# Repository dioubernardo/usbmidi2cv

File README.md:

# USB MIDI to CV

Project inspired by [elkayem/midi2cv](https://github.com/elkayem/midi2cv), but using MIDI over USB communication.

## Requirements

- Arduino Leonardo or any board based on ATmega32u4 or ARM ([MIDIUSB compatibility](https://docs.arduino.cc/libraries/midiusb/#Compatibility))  
- MCP4728 (PCBs are designed for the generic GY-MCP4728 module)  
- LM324N  
- Some resistors and connectors

> ⚠️ The resistors connected to the A output of the LM324N don't need to match exact values, as long as they maintain an amplification ratio of approximately 1.77. Inaccurate values may affect 1V/Oct tuning.

The operational amplifier is configured as a non-inverting amplifier with the following resistors:

- **R1 = 10kΩ** (between the inverting input and GND)
- **R2 = 6.8kΩ + 900Ω _(from trimpot)_ = 7.7kΩ** (between the output and the inverting input)

The amplification factor (gain) is calculated as:

Amplification = 1 + (R2/R1) = 1 + (7.7kΩ/10kΩ) = 1.77

Therefore, the gain is **1.77x**.

## How It Works

- When a MIDI note is received (regardless of channel), it is converted to CV in 1V/Oct format, with C0 = 0V, C1 = 1V, C2 = 2V... covering 88 notes total.
- When a second note is played, it replaces the previous one, which is kept in a buffer.
- **Velocity** is converted to a voltage ranging from 0V to 4V.
- A **Trigger Pulse** of 5V is sent for 20ms every time a note is triggered.
- The **Gate** stays high (5V) while any note is being played.
- **Pitch Bend** is centered at 0.5V and ranges from 0V to 1V.
- Any **Control Change (CC)** message is converted to a voltage from 0V to 4V.

## Schematic

The file [`usbmidi2cv.sch`](https://github.com/dioubernardo/usbmidi2cv/blob/main/usbmidi2cv.sch) contains the schematic and can be edited using Eagle.

## PCB

Designed to work as an Arduino shield, this PCB can be easily etched on a single-sided copper board for DIY builds.

The file [`usbmidi2cv.brd`](https://github.com/dioubernardo/usbmidi2cv/blob/main/usbmidi2cv.brd) contains the PCB layout, also editable in Eagle.

To print, use the file [pcb.pdf](https://github.com/dioubernardo/usbmidi2cv/blob/main/pcb.pdf).

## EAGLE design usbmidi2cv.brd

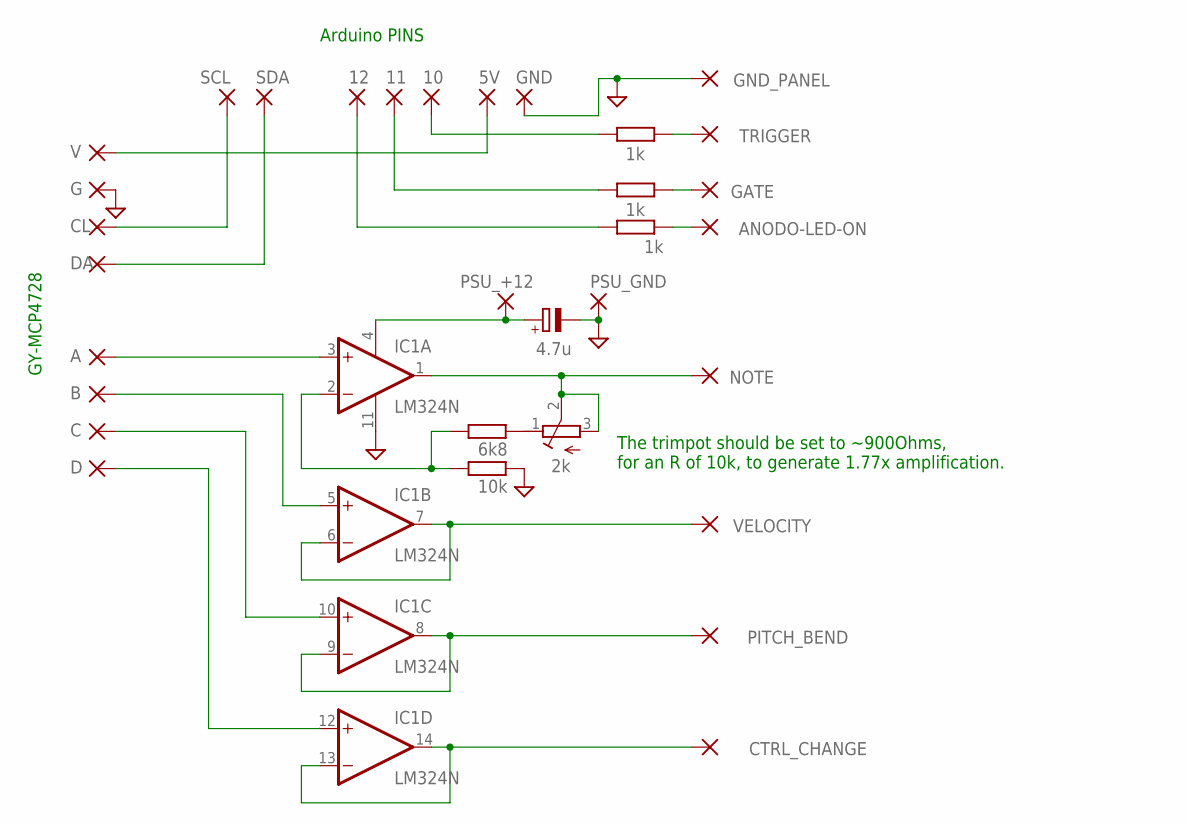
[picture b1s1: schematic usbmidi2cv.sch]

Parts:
5V, 10, 11, 12: 1,6/0,8
A: 1,6/0,8
ANODO-LED-ON: 1,6/0,8
B: 1,6/0,8
C: 1,6/0,8
C1: 4.7u; E2,5-6
CL: 1,6/0,8
CTRL_CHANGE: 1,6/0,8
D: 1,6/0,8
DA: 1,6/0,8
G: 1,6/0,8
GATE: 1,6/0,8
GND: 1,6/0,8
GND_PANEL: 1,6/0,8
IC1: LM324N; DIL14
NOTE: 1,6/0,8
PITCH_BEND: 1,6/0,8
PSU_+12: 1,6/0,8
PSU_GND: 1,6/0,8
R1, R2, R3: 1k; 0204/7
R4: 10k; 0207/12
R5: 2k; RTRIM3006P
R6: 6k8; 0207/12
SCL: 1,6/0,8
SDA: 1,6/0,8
TRIGGER: 1,6/0,8
V: 1,6/0,8
VELOCITY: 1,6/0,8

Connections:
GND: C1.-, G.1, GND.1, GND_PANEL.1, IC1.11 (V-), PSU_GND.1, R4.2
unnamed: A.1, IC1.3 (+IN)
unnamed: R2.1, TRIGGER.1
unnamed: GATE.1, R1.1
unnamed: 10.1, R2.2
unnamed: 11.1, R1.2
unnamed: ANODO-LED-ON.1, R3.1
unnamed: 12.1, R3.2
unnamed: 5V.1, V.1
unnamed: CL.1, SCL.1
unnamed: DA.1, SDA.1
unnamed: B.1, IC1.5 (+IN)
unnamed: C.1, IC1.10 (+IN)
unnamed: CTRL_CHANGE.1, IC1.13 (-IN), IC1.14 (OUT)
unnamed: IC1.1 (OUT), NOTE.1, R5.2 (S), R5.3 (A)
unnamed: IC1.8 (OUT), IC1.9 (-IN), PITCH_BEND.1
unnamed: IC1.6 (-IN), IC1.7 (OUT), VELOCITY.1
unnamed: IC1.2 (-IN), R4.1, R6.1
unnamed: R5.1 (E), R6.2
unnamed: C1.+, IC1.4 (V+), PSU_+12.1
unnamed: D.1, IC1.12 (+IN)

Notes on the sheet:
Arduino PINS
GY-MCP4728
The trimpot should be set to ~900Ohms, for an R of 10k, to generate 1.77x amplification.

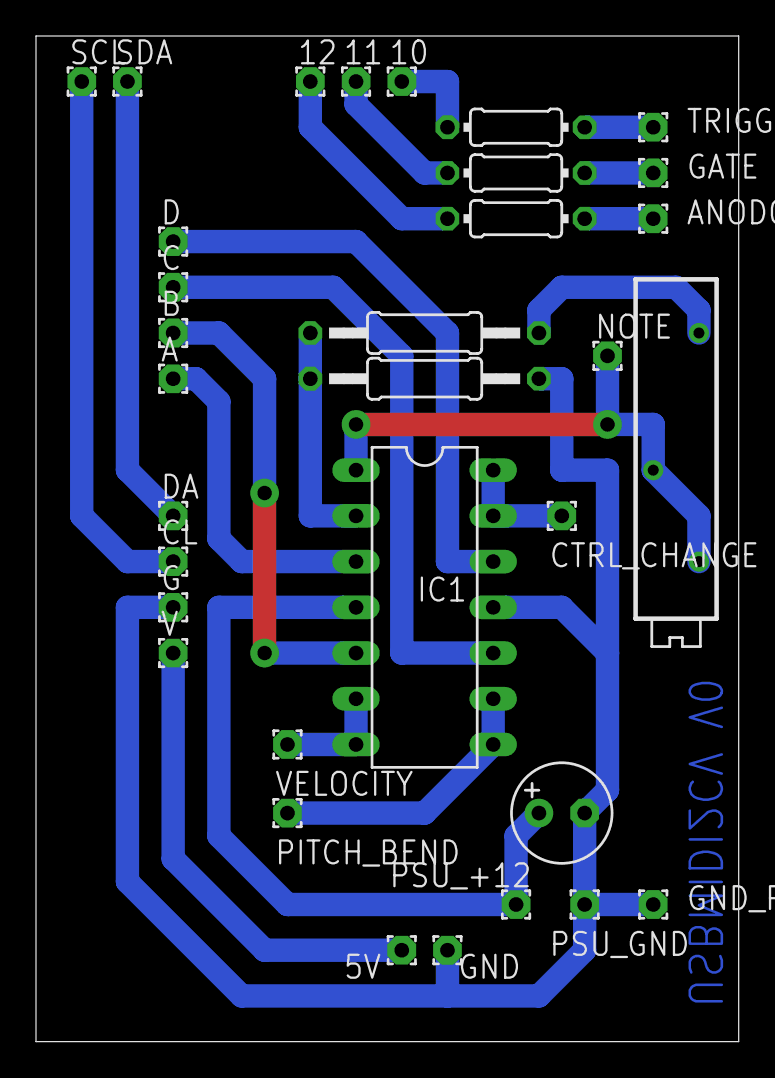
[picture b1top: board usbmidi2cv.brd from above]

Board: 2 copper layers, 39.0 x 55.9 mm, 33 parts (0 on the bottom side), 21 nets.

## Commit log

2025-04-17 melhorias na documentação
2025-04-17 equation
2025-04-17 amplification
2025-04-17 modificações
2025-04-17 correção de elemento perdido
2025-05-22 melhorias na pcb
2025-05-22 update image
2025-06-18 change soldpad size
